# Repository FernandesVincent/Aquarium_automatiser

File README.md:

# Aquarium_automatiser
Suite du projet 2425_Maker_Aquarium

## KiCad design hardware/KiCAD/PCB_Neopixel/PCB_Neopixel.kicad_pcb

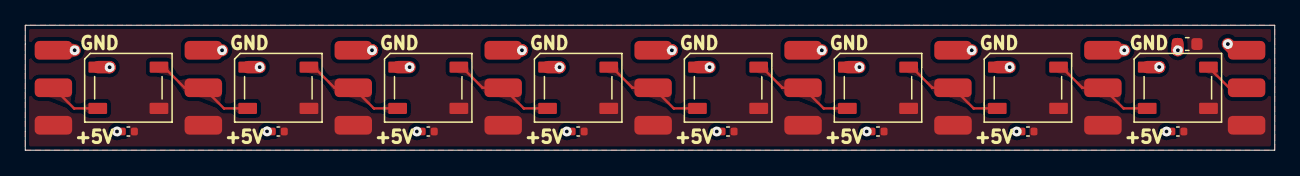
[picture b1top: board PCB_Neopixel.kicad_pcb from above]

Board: 2 copper layers, 100.0 x 10.0 mm, 44 parts (0 on the bottom side), 11 nets.

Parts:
C201, C301, C401, C501, C601, C701, C801, C901: 100n; C_0402_1005Metric
C1201: 10u; C_0603_1608Metric
D201, D301, D401, D501, D601, D701, D801, D901: WS2812B; LED_WS2812B_PLCC4_5.0x5.0mm_P3.2mm
J201, J202, J203, J301, J302, J303, J401, J402, J403, J501, J502, J503, J601, J602, J603, J701, J702, J703, J801, J802, J803, J901, J902, J903, J1201, J1202, J1203: Conn_01x01; SolderWirePad_1x01_SMD_1.5x3mm

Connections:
+5V: C201.1, C301.1, C401.1, C501.1, C601.1, C701.1, C801.1, C901.1, C1201.1, D201.1 (VDD), D301.1 (VDD), D401.1 (VDD), D501.1 (VDD), D601.1 (VDD), D701.1 (VDD), D801.1 (VDD), D901.1 (VDD), J201.1, J301.1, J401.1, J501.1, J601.1, J701.1, J801.1, J901.1, J1201.1
/Segment/DI: D201.4 (DIN), J203.1
DO1: D201.2 (DOUT), D301.4 (DIN), J303.1
DO2: D301.2 (DOUT), D401.4 (DIN), J403.1
DO3: D401.2 (DOUT), D501.4 (DIN), J503.1
DO4: D501.2 (DOUT), D601.4 (DIN), J603.1
DO5: D601.2 (DOUT), D701.4 (DIN), J703.1
DO6: D701.2 (DOUT), D801.4 (DIN), J803.1
DO7: D801.2 (DOUT), D901.4 (DIN), J903.1
DO8: D901.2 (DOUT), J1203.1
GND: C201.2, C301.2, C401.2, C501.2, C601.2, C701.2, C801.2, C901.2, C1201.2, D201.3 (VSS), D301.3 (VSS), D401.3 (VSS), D501.3 (VSS), D601.3 (VSS), D701.3 (VSS), D801.3 (VSS), D901.3 (VSS), J202.1, J302.1, J402.1, J502.1, J602.1, J702.1, J802.1, J902.1, J1202.1

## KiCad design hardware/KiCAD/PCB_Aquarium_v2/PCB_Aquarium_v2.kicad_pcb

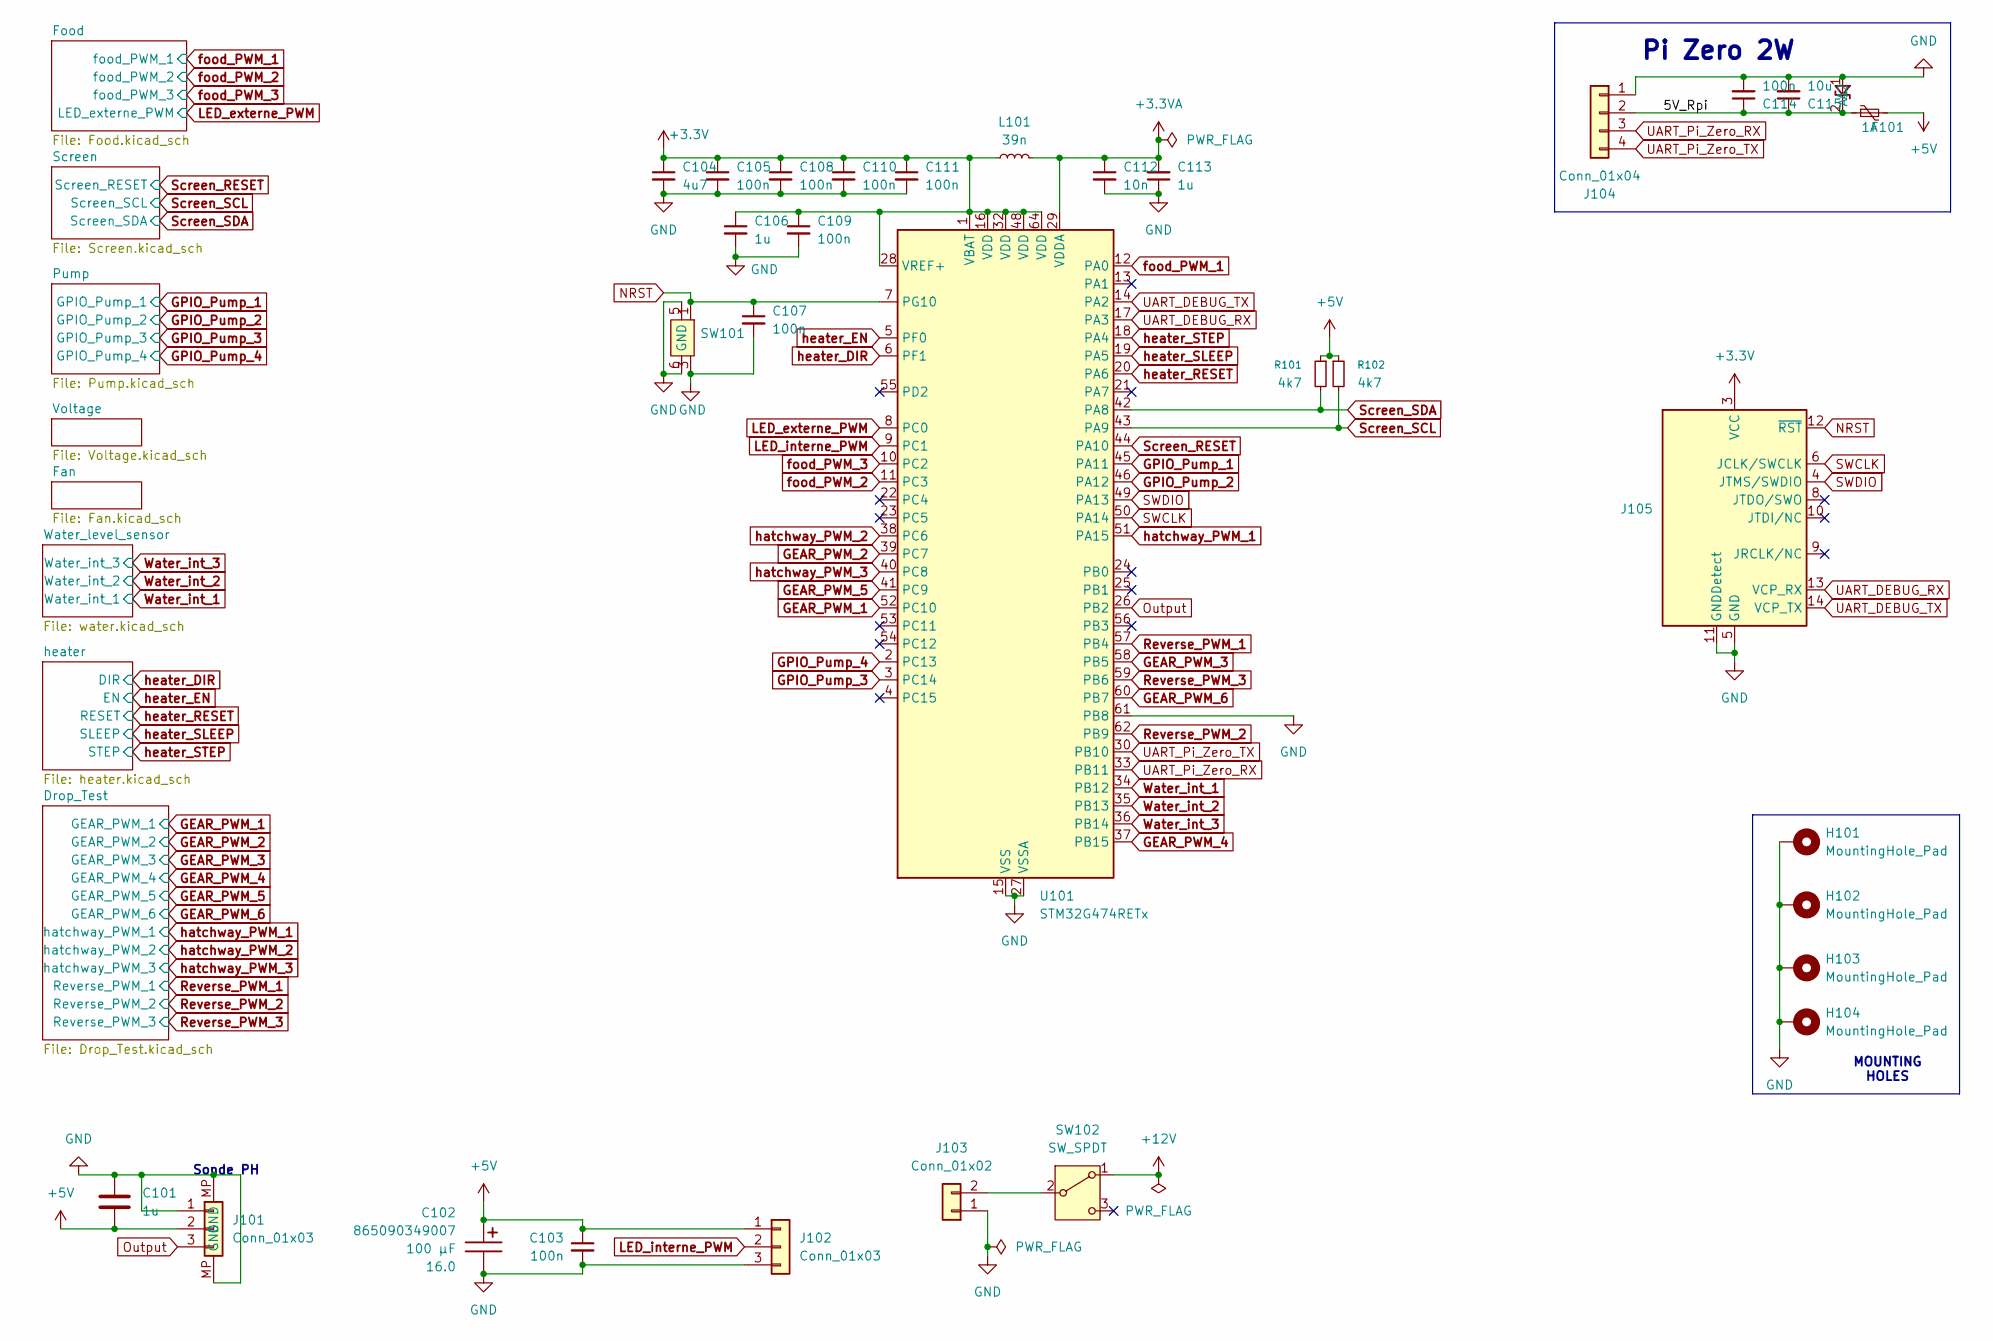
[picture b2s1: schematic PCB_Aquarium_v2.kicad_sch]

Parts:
C101: 1u; C_0603_1608Metric
C102: D8L6.5_865090349007; CP_Wurth_WCAP-ASLU-D8L6.5; Voltage 16.0; Part Number 865090349007
C103, C105, C107, C108, C109, C110, C111, C114: 100n; C_0402_1005Metric
C104: 4u7; C_0603_1608Metric
C106, C113: 1u; C_0402_1005Metric
C112: 10n; C_0402_1005Metric
C115: 10u; C_0603_1608Metric
D101: D_SOD-523
F101: 1A; Fuse_2920_7451Metric; MPN 0ZAF0013FF28
H101, H102, H103, H104: MountingHole_Pad; MountingHole_3.2mm_M3_Pad_Via
J101: Conn_01x03; JST_SH_BM03B-SRSS-TB_1x03-1MP_P1.00mm_Vertical
J102: Conn_01x03; JST_PH_B3B-PH-K_1x03_P2.00mm_Vertical
J103: Conn_01x02; AMASS_XT30U-M_1x02_P5.0mm_Vertical
J104: Conn_01x04; JST_PH_B4B-PH-K_1x04_P2.00mm_Vertical
J105: Conn_ST_STDC14; PinHeader_2x07_P1.27mm_Vertical_SMD; MPN STLINK-V3MINIE
L101: 39n; L_0603_1608Metric
R101, R102: 4k7; R_0201_0603Metric
SW101: WS-TASV SMT Tact Switch 3.0 x 2.6 mm
SW102: SW_SPDT; SW_Wurth_WS-TOTV_472123020421
U101: STM32G474RETx; LQFP-64_10x10mm_P0.5mm

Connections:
+3.3V: C104.1, C105.1, C106.1, C108.1, C109.1, C110.1, C111.1, J105.3 (VCC), L101.1, U101.1 (VBAT), U101.16 (VDD), U101.28 (VREF+), U101.32 (VDD), U101.48 (VDD), U101.64 (VDD); also elsewhere on the board
+3.3VA: C112.1, C113.2, L101.2, U101.29 (VDDA)
+5V: C101.1, C102.1, C103.1, F101.2, J101.2, J102.1, R101.1, R102.1; also elsewhere on the board
+12V: SW102.1 (A); also elsewhere on the board
/5V_Rpi: C114.1, C115.1, D101.2 (A2), F101.1, J104.2
GEAR_PWM_1: U101.52 (PC10); also elsewhere on the board
GEAR_PWM_2: U101.39 (PC7); also elsewhere on the board
GEAR_PWM_3: U101.58 (PB5); also elsewhere on the board
GEAR_PWM_4: U101.37 (PB15); also elsewhere on the board
GEAR_PWM_5: U101.41 (PC9); also elsewhere on the board
GEAR_PWM_6: U101.60 (PB7); also elsewhere on the board
GND: C101.2, C102.2, C103.2, C104.2, C105.2, C106.2, C107.2, C108.2, C109.2, C110.2, C111.2, C112.2, C113.1, C114.2, C115.2, D101.1 (A1), H101.1, H102.1, H103.1, H104.1, J101.1, J101.MP (GND), J102.3, J103.1, J104.1, J105.5 (GND), J105.7 (GND), J105.11 (GNDDetect), SW101.3, SW101.4, SW101.5, SW101.6 (GND), U101.15 (VSS), U101.27 (VSSA), U101.31 (VSS), U101.47 (VSS), U101.61 (PB8), U101.63 (VSS); also elsewhere on the board
GPIO_Pump_1: U101.45 (PA11); also elsewhere on the board
GPIO_Pump_2: U101.46 (PA12); also elsewhere on the board
GPIO_Pump_3: U101.3 (PC14); also elsewhere on the board
GPIO_Pump_4: U101.2 (PC13); also elsewhere on the board
LED_externe_PWM: U101.8 (PC0); also elsewhere on the board
LED_interne_PWM: J102.2, U101.9 (PC1)
NRST: C107.1, J105.12 (~RST), SW101.1, SW101.2, U101.7 (PG10)
unnamed: J103.2, SW102.2 (B)
Output: J101.3, U101.26 (PB2)
Reverse_PWM_1: U101.57 (PB4); also elsewhere on the board
Reverse_PWM_2: U101.62 (PB9); also elsewhere on the board
Reverse_PWM_3: U101.59 (PB6); also elsewhere on the board
SWCLK: J105.6 (JCLK/SWCLK), U101.50 (PA14)
SWDIO: J105.4 (JTMS/SWDIO), U101.49 (PA13)
Screen_RESET: U101.44 (PA10); also elsewhere on the board
Screen_SCL: R102.2, U101.43 (PA9); also elsewhere on the board
Screen_SDA: R101.2, U101.42 (PA8); also elsewhere on the board
UART_DEBUG_RX: J105.13 (VCP_RX), U101.17 (PA3)
UART_DEBUG_TX: J105.14 (VCP_TX), U101.14 (PA2)
UART_Pi_Zero_RX: J104.3, U101.33 (PB11)
UART_Pi_Zero_TX: J104.4, U101.30 (PB10)
Water_int_1: U101.34 (PB12); also elsewhere on the board
Water_int_2: U101.35 (PB13); also elsewhere on the board
Water_int_3: U101.36 (PB14); also elsewhere on the board
food_PWM_1: U101.12 (PA0); also elsewhere on the board
food_PWM_2: U101.11 (PC3); also elsewhere on the board
food_PWM_3: U101.10 (PC2); also elsewhere on the board
hatchway_PWM_1: U101.51 (PA15); also elsewhere on the board
hatchway_PWM_2: U101.38 (PC6); also elsewhere on the board
hatchway_PWM_3: U101.40 (PC8); also elsewhere on the board
heater_DIR: U101.6 (PF1); also elsewhere on the board
heater_EN: U101.5 (PF0); also elsewhere on the board
heater_RESET: U101.20 (PA6); also elsewhere on the board
heater_SLEEP: U101.19 (PA5); also elsewhere on the board
heater_STEP: U101.18 (PA4); also elsewhere on the board

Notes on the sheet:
Sonde PH
Pi Zero 2W
MOUNTING HOLES

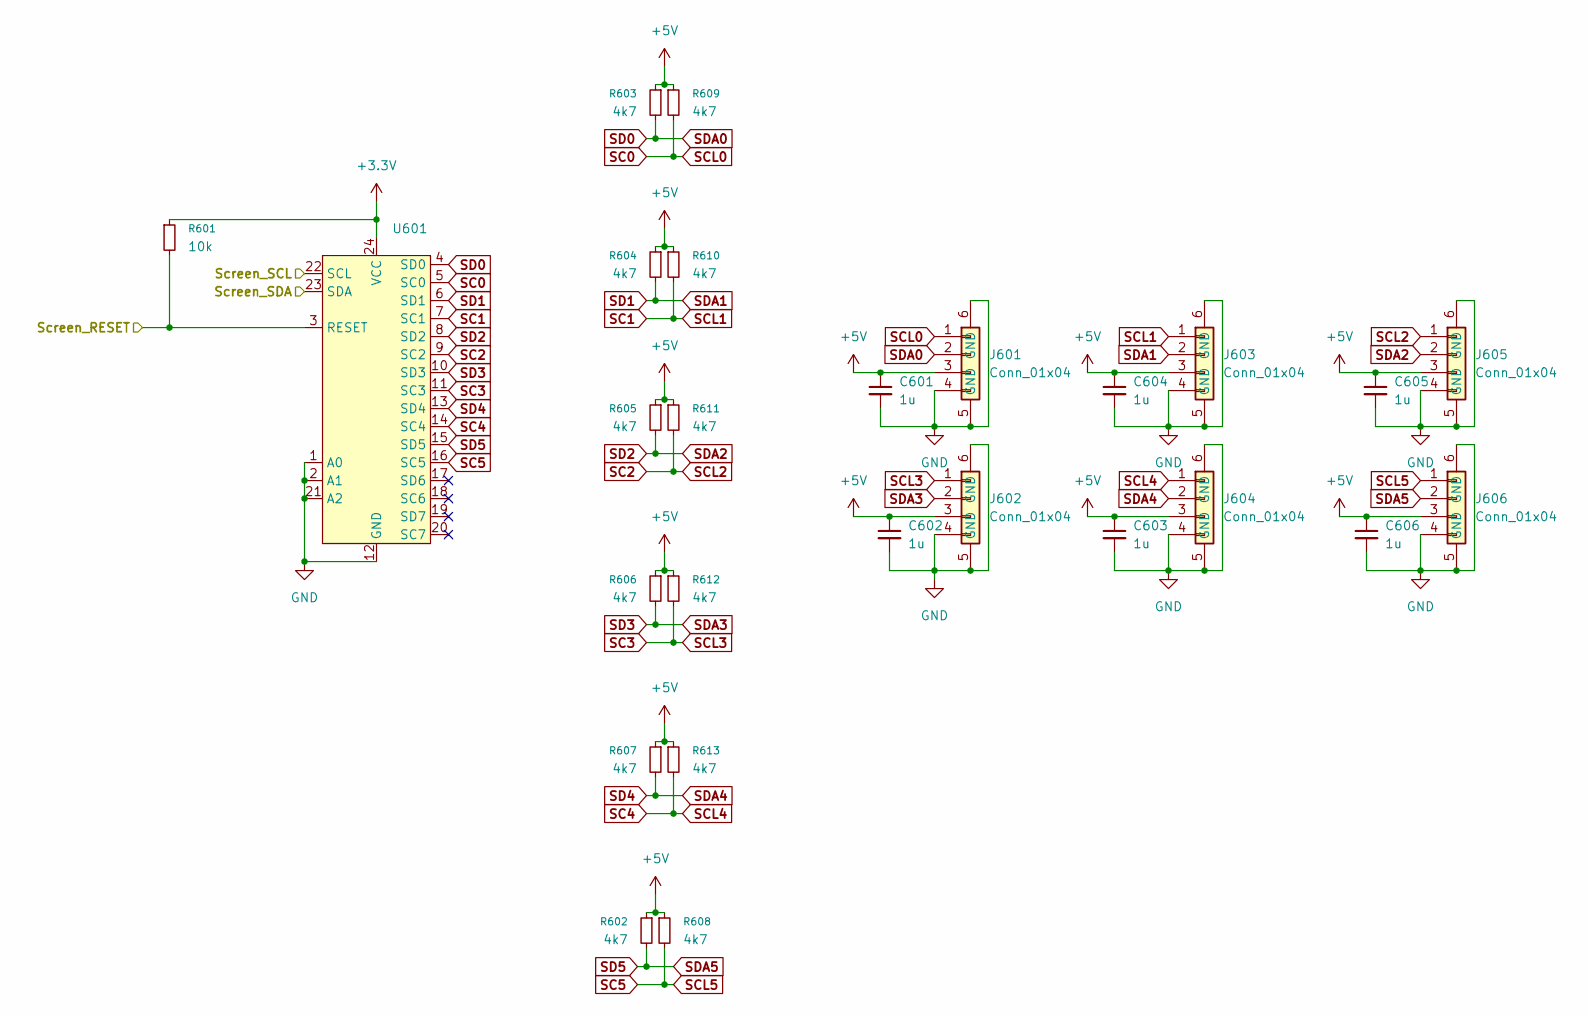
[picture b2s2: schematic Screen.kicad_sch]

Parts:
C601, C602, C603, C604, C605, C606: 1u; C_0603_1608Metric
J601, J602, J603, J604, J605, J606: Conn_01x04; Wurth_Vertical_4_pos_0.8mm
R601: 10k; R_0402_1005Metric
R602, R603, R604, R605, R606, R607, R608, R609, R610, R611, R612, R613: 4k7; R_0201_0603Metric
U601: TSSOP-24_4.4x7.8mm_P0.65mm; MPN PI4MSD5V9547LEX

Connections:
+3.3V: R601.1, U601.24 (VCC); also elsewhere on the board
+5V: C601.1, C602.1, C603.1, C604.1, C605.1, C606.1, J601.3, J602.3, J603.3, J604.3, J605.3, J606.3, R602.1, R603.1, R604.1, R605.1, R606.1, R607.1, R608.1, R609.1, R610.1, R611.1, R612.1, R613.1; also elsewhere on the board
GND: C601.2, C602.2, C603.2, C604.2, C605.2, C606.2, J601.4, J601.5 (GND), J601.6 (GND), J602.4, J602.5 (GND), J602.6 (GND), J603.4, J603.5 (GND), J603.6 (GND), J604.4, J604.5 (GND), J604.6 (GND), J605.4, J605.5 (GND), J605.6 (GND), J606.4, J606.5 (GND), J606.6 (GND), U601.1 (A0), U601.2 (A1), U601.12 (GND), U601.21 (A2); also elsewhere on the board
SC0: J601.1, R609.2, U601.5 (SC0)
SC1: J603.1, R610.2, U601.7 (SC1)
SC2: J605.1, R611.2, U601.9 (SC2)
SC3: J602.1, R612.2, U601.11 (SC3)
SC4: J604.1, R613.2, U601.14 (SC4)
SC5: J606.1, R608.2, U601.16 (SC5)
SD0: J601.2, R603.2, U601.4 (SD0)
SD1: J603.2, R604.2, U601.6 (SD1)
SD2: J605.2, R605.2, U601.8 (SD2)
SD3: J602.2, R606.2, U601.10 (SD3)
SD4: J604.2, R607.2, U601.13 (SD4)
SD5: J606.2, R602.2, U601.15 (SD5)
Screen_RESET: R601.2, U601.3 (RESET); also elsewhere on the board
Screen_SCL: U601.22 (SCL); also elsewhere on the board
Screen_SDA: U601.23 (SDA); also elsewhere on the board

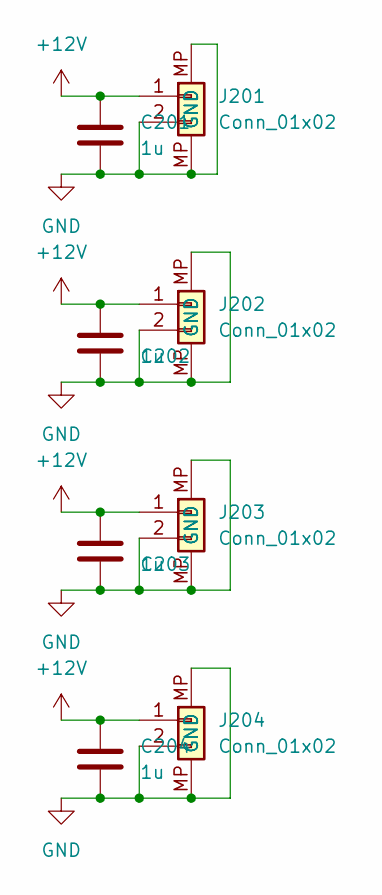
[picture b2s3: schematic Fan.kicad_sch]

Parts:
C201, C202, C203, C204: 1u; C_0603_1608Metric
J201, J202, J203, J204: Conn_01x02; JST_SH_BM02B-SRSS-TB_1x02-1MP_P1.00mm_Vertical

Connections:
+12V: C201.2, C202.2, C203.2, C204.2, J201.1, J202.1, J203.1, J204.1; also elsewhere on the board
GND: C201.1, C202.1, C203.1, C204.1, J201.2, J201.MP (GND), J202.2, J202.MP (GND), J203.2, J203.MP (GND), J204.2, J204.MP (GND); also elsewhere on the board

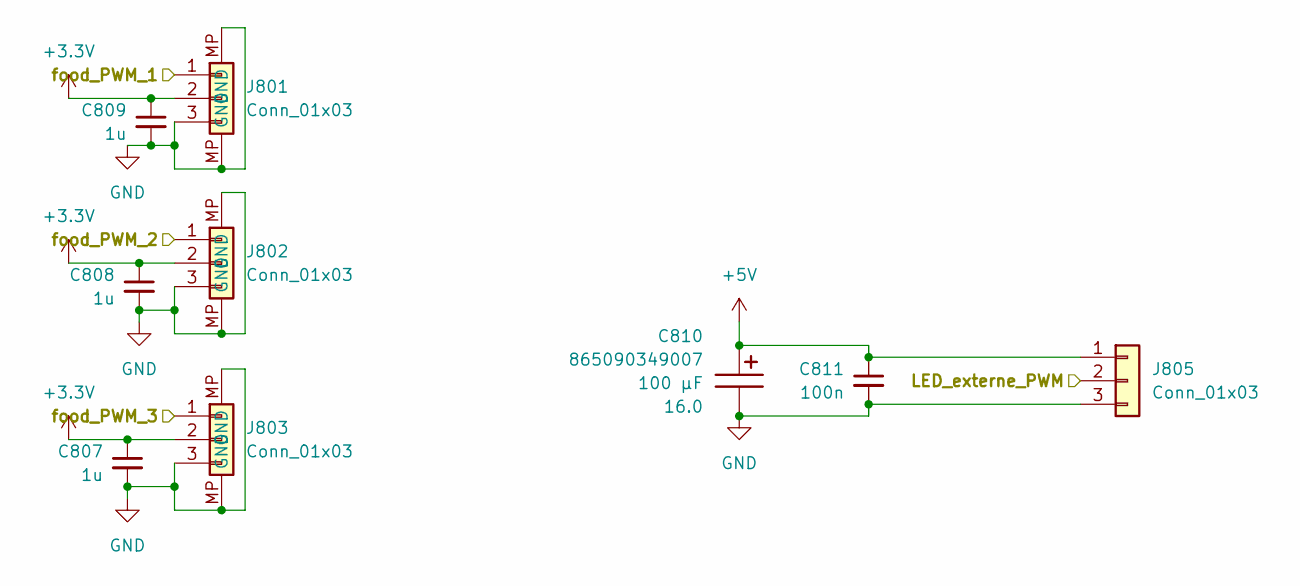
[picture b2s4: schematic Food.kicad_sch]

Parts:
C807, C808, C809: 1u; C_0603_1608Metric
C810: D8L6.5_865090349007; CP_Wurth_WCAP-ASLU-D8L6.5; Voltage 16.0; Part Number 865090349007
C811: 100n; C_0402_1005Metric
J801, J802, J803: Conn_01x03; JST_SH_BM03B-SRSS-TB_1x03-1MP_P1.00mm_Vertical
J805: Conn_01x03; JST_PH_B3B-PH-K_1x03_P2.00mm_Vertical

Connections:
+3.3V: C807.1, C808.1, C809.1, J801.2, J802.2, J803.2; also elsewhere on the board
+5V: C810.1, C811.1, J805.1; also elsewhere on the board
GND: C807.2, C808.2, C809.2, C810.2, C811.2, J801.3, J801.MP (GND), J802.3, J802.MP (GND), J803.3, J803.MP (GND), J805.3; also elsewhere on the board
LED_externe_PWM: J805.2; also elsewhere on the board
food_PWM_1: J801.1; also elsewhere on the board
food_PWM_2: J802.1; also elsewhere on the board
food_PWM_3: J803.1; also elsewhere on the board

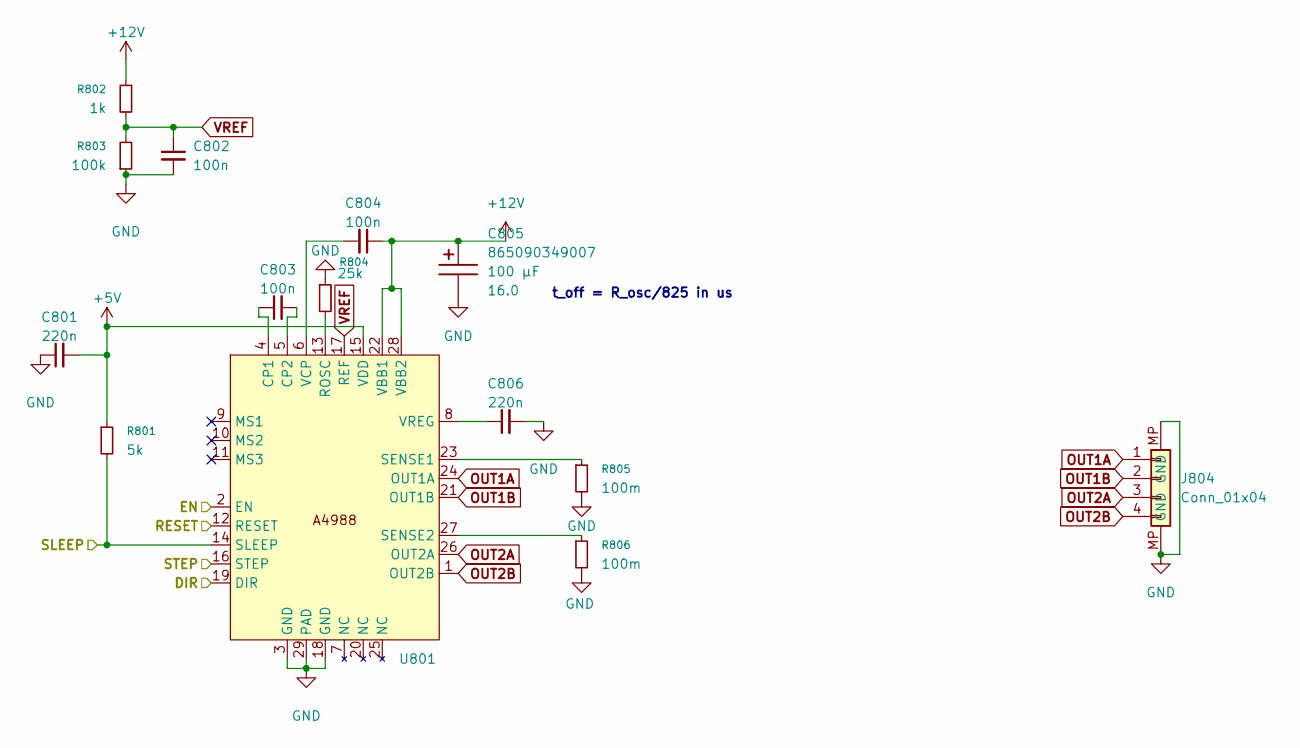
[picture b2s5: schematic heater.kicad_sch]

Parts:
C801, C806: 220n; C_0402_1005Metric
C802, C803, C804: 100n; C_0402_1005Metric
C805: D8L6.5_865090349007; CP_Wurth_WCAP-ASLU-D8L6.5; Voltage 16.0; Part Number 865090349007
J804: Conn_01x04; JST_SH_BM04B-SRSS-TB_1x04-1MP_P1.00mm_Vertical
R801: 5k; R_0402_1005Metric
R802: 1k; R_0402_1005Metric
R803: 100k; R_0402_1005Metric
R804: 25k; R_0402_1005Metric
R805, R806: 100m; R_0603_1608Metric; MPN 560050316001
U801: QFN-28-1EP_5x5mm_P0.5mm_EP2.7x2.7mm

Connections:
+5V: C801.2, R801.1, U801.15 (VDD); also elsewhere on the board
+12V: C804.1, C805.1, R802.1, U801.22 (VBB1), U801.28 (VBB2); also elsewhere on the board
GND: C801.1, C802.2, C805.2, C806.2, J804.MP (GND), R803.1, R804.1, R805.2, R806.2, U801.3 (GND), U801.18 (GND), U801.29 (PAD); also elsewhere on the board
unnamed: C803.1, U801.4 (CP1)
unnamed: C803.2, U801.5 (CP2)
unnamed: R804.2, U801.13 (ROSC)
unnamed: R805.1, U801.23 (SENSE1)
unnamed: R806.1, U801.27 (SENSE2)
unnamed: C804.2, U801.6 (VCP)
unnamed: C806.1, U801.8 (VREG)
OUT1A: J804.1, U801.24 (OUT1A)
OUT1B: J804.2, U801.21 (OUT1B)
OUT2A: J804.3, U801.26 (OUT2A)
OUT2B: J804.4, U801.1 (OUT2B)
VREF: C802.1, R802.2, R803.2, U801.17 (REF)
heater_DIR: U801.19 (DIR); also elsewhere on the board
heater_EN: U801.2 (EN); also elsewhere on the board
heater_RESET: U801.12 (RESET); also elsewhere on the board
heater_SLEEP: R801.2, U801.14 (SLEEP); also elsewhere on the board
heater_STEP: U801.16 (STEP); also elsewhere on the board

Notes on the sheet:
t_off = R_osc/825 in us

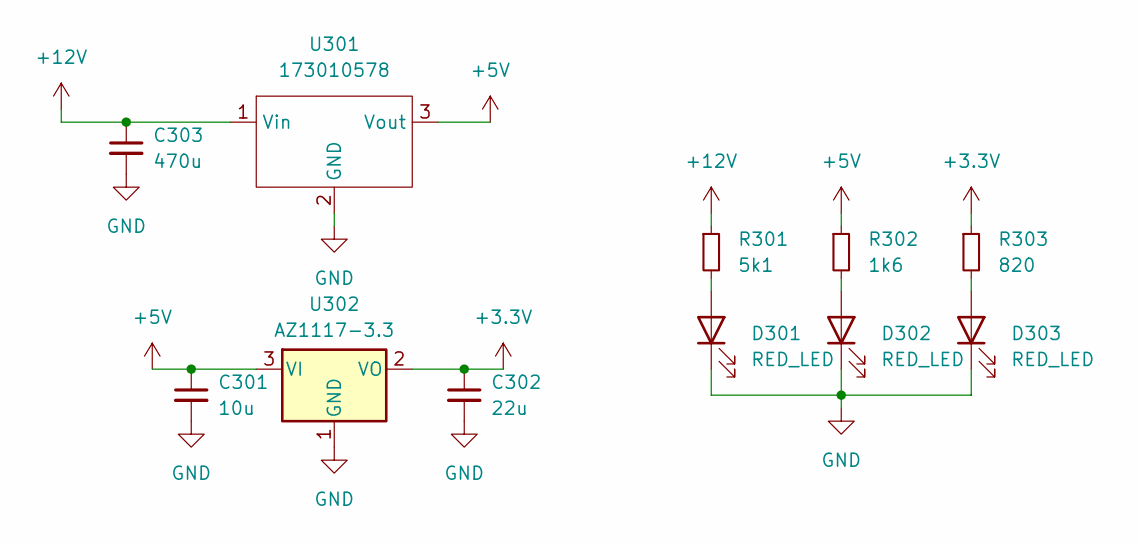
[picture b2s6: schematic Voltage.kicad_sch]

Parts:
C301: 10u; C_0603_1608Metric
C302: 22u; C_Elec_5x5.4
C303: 470u; C_Elec_10x10.2
D301, D302, D303: RED_LED; LED_0603_1608Metric; MPN 150060RS55040
R301: 5k1; R_0402_1005Metric
R302: 1k6; R_0402_1005Metric
R303: 820; R_0402_1005Metric
U301: 173010578; 173010542; MPN 173010578
U302: AZ1117-3.3; SOT-223-3_TabPin2; MPN AZ1117CH2-3.3TRG1

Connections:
+3.3V: C302.1, R303.1, U302.2 (VO); also elsewhere on the board
+5V: C301.1, R302.1, U301.3 (Vout), U302.3 (VI); also elsewhere on the board
+12V: C303.1, R301.1, U301.1 (Vin); also elsewhere on the board
GND: C301.2, C302.2, C303.2, D301.1 (K), D302.1 (K), D303.1 (K), U301.2 (GND), U302.1 (GND); also elsewhere on the board
unnamed: D301.2 (A), R301.2
unnamed: D302.2 (A), R302.2
unnamed: D303.2 (A), R303.2

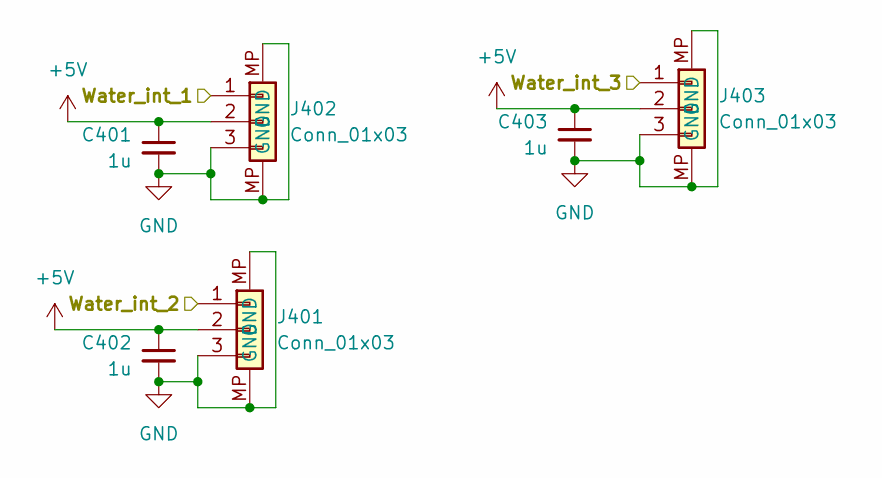
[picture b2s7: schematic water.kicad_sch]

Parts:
C401, C402, C403: 1u; C_0603_1608Metric
J401, J402, J403: Conn_01x03; JST_SH_BM03B-SRSS-TB_1x03-1MP_P1.00mm_Vertical

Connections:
+5V: C401.1, C402.1, C403.1, J401.2, J402.2, J403.2; also elsewhere on the board
GND: C401.2, C402.2, C403.2, J401.3, J401.MP (GND), J402.3, J402.MP (GND), J403.3, J403.MP (GND); also elsewhere on the board
Water_int_1: J402.1; also elsewhere on the board
Water_int_2: J401.1; also elsewhere on the board
Water_int_3: J403.1; also elsewhere on the board

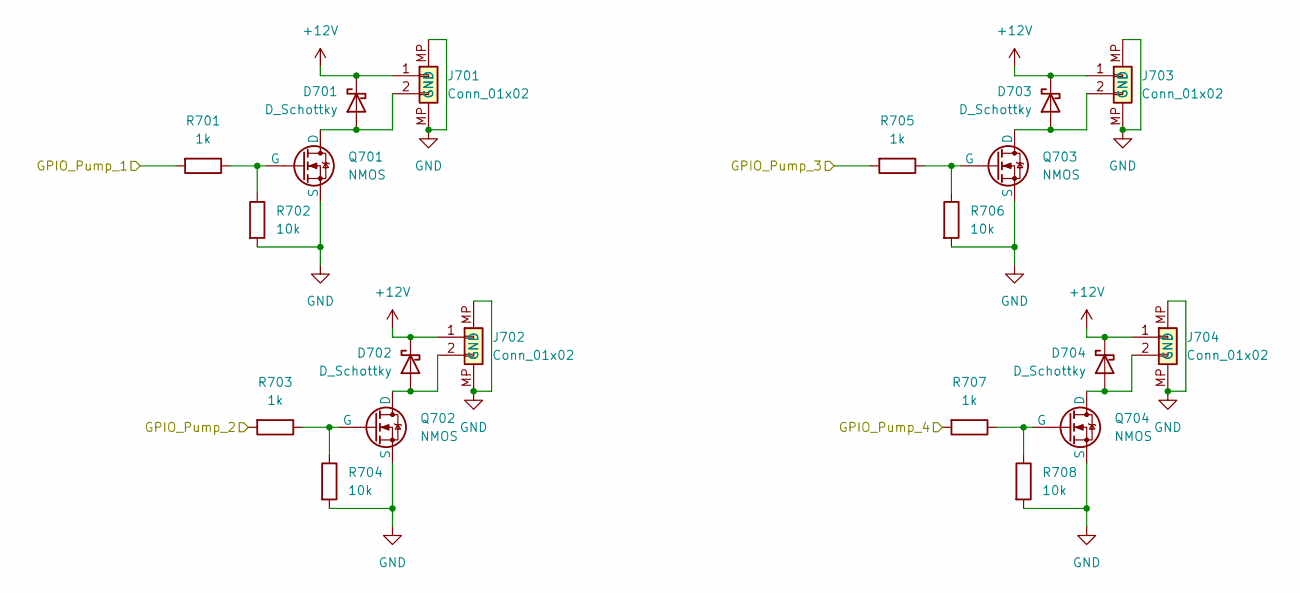
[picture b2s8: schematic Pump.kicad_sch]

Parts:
D701, D702, D703, D704: D_Schottky; FSV330AF; MPN FSV340AF
J701, J702, J703, J704: Conn_01x02; JST_SH_BM02B-SRSS-TB_1x02-1MP_P1.00mm_Vertical
Q701, Q702, Q703, Q704: NMOS; SOT-23; MPN SQ2310ES-T1_BE3
R701, R703, R705, R707: 1k; R_0402_1005Metric
R702, R704, R706, R708: 10k; R_0402_1005Metric

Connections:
+12V: D701.1 (K), D702.1 (K), D703.1 (K), D704.1 (K), J701.1, J702.1, J703.1, J704.1; also elsewhere on the board
GND: J701.MP (GND), J702.MP (GND), J703.MP (GND), J704.MP (GND), Q701.3 (S), Q702.3 (S), Q703.3 (S), Q704.3 (S), R702.2, R704.2, R706.2, R708.2; also elsewhere on the board
GPIO_Pump_1: R701.2; also elsewhere on the board
GPIO_Pump_2: R703.2; also elsewhere on the board
GPIO_Pump_3: R705.2; also elsewhere on the board
GPIO_Pump_4: R707.2; also elsewhere on the board
unnamed: D701.2 (A), J701.2, Q701.1 (D)
unnamed: D702.2 (A), J702.2, Q702.1 (D)
unnamed: D703.2 (A), J703.2, Q703.1 (D)
unnamed: D704.2 (A), J704.2, Q704.1 (D)
unnamed: Q701.2 (G), R701.1, R702.1
unnamed: Q702.2 (G), R703.1, R704.1
unnamed: Q703.2 (G), R705.1, R706.1
unnamed: Q704.2 (G), R707.1, R708.1

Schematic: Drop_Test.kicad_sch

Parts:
C901, C902, C903, C904, C905, C906, C907, C908, C909, C910, C911, C912: 1u; C_0603_1608Metric
J901, J902, J903, J904, J905, J906, J907, J908, J909, J910, J911, J912: Conn_01x03; JST_SH_BM03B-SRSS-TB_1x03-1MP_P1.00mm_Vertical

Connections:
+3.3V: C901.1, C902.1, C903.1, C904.1, C905.1, C906.1, C907.1, C908.1, C909.1, C910.1, C911.1, C912.1, J901.2, J902.2, J903.2, J904.2, J905.2, J906.2, J907.2, J908.2, J909.2, J910.2, J911.2, J912.2; also elsewhere on the board
GEAR_PWM_1: J909.1; also elsewhere on the board
GEAR_PWM_2: J907.1; also elsewhere on the board
GEAR_PWM_3: J908.1; also elsewhere on the board
GEAR_PWM_4: J906.1; also elsewhere on the board
GEAR_PWM_5: J904.1; also elsewhere on the board
GEAR_PWM_6: J905.1; also elsewhere on the board
GND: C901.2, C902.2, C903.2, C904.2, C905.2, C906.2, C907.2, C908.2, C909.2, C910.2, C911.2, C912.2, J901.3, J901.MP (GND), J902.3, J902.MP (GND), J903.3, J903.MP (GND), J904.3, J904.MP (GND), J905.3, J905.MP (GND), J906.3, J906.MP (GND), J907.3, J907.MP (GND), J908.3, J908.MP (GND), J909.3, J909.MP (GND), J910.3, J910.MP (GND), J911.3, J911.MP (GND), J912.3, J912.MP (GND); also elsewhere on the board
Reverse_PWM_1: J903.1; also elsewhere on the board
Reverse_PWM_2: J901.1; also elsewhere on the board
Reverse_PWM_3: J902.1; also elsewhere on the board
hatchway_PWM_1: J912.1; also elsewhere on the board
hatchway_PWM_2: J910.1; also elsewhere on the board
hatchway_PWM_3: J911.1; also elsewhere on the board

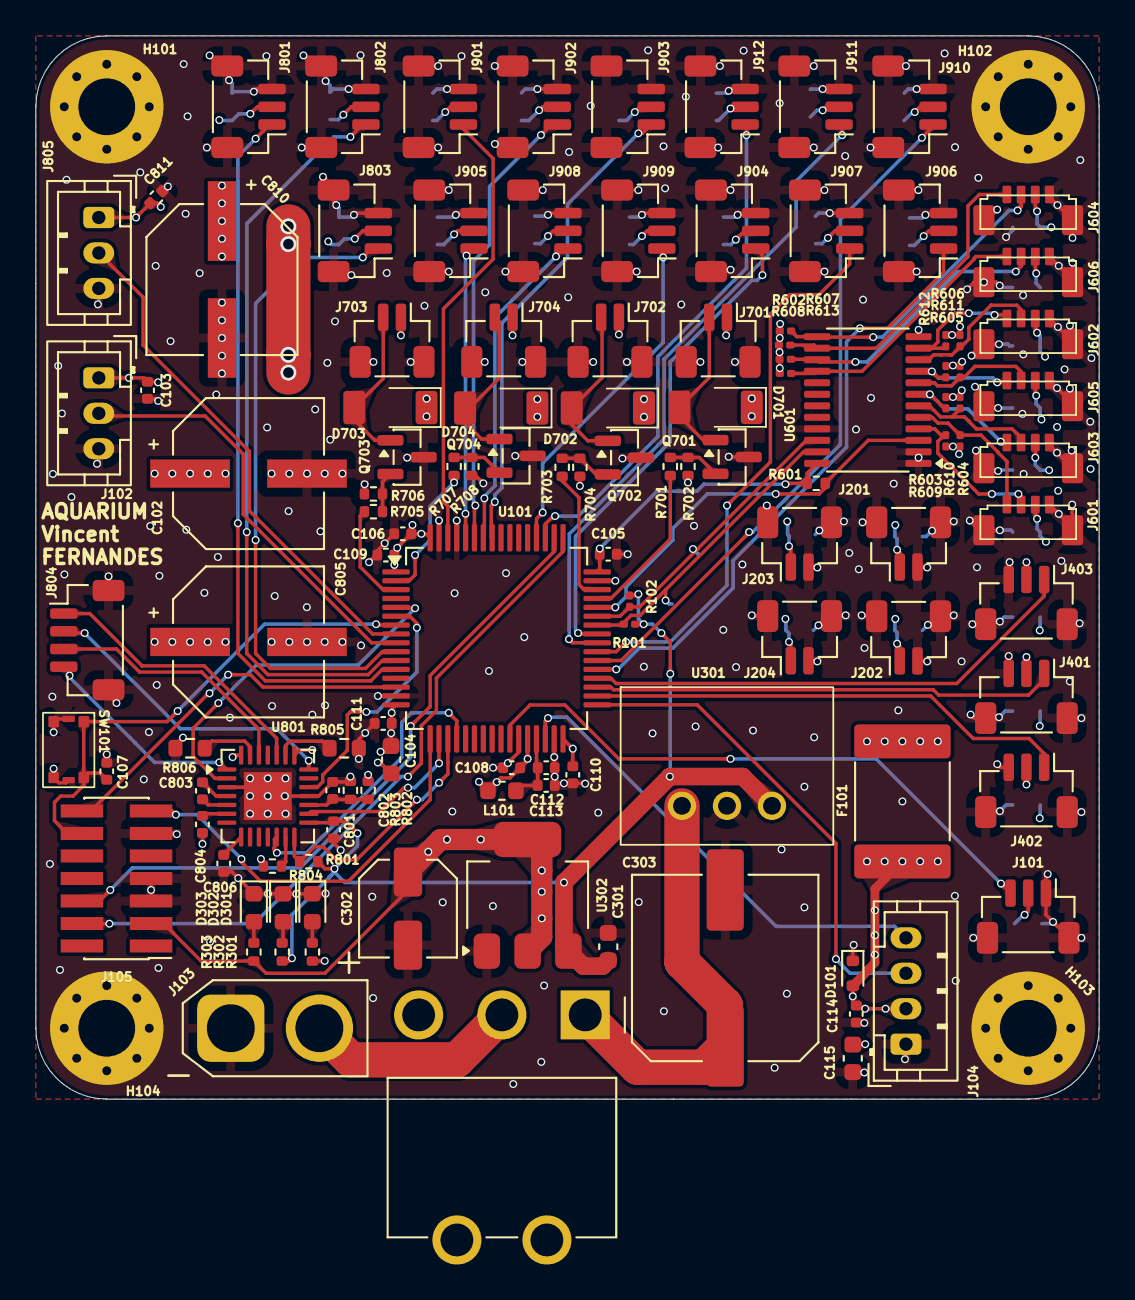
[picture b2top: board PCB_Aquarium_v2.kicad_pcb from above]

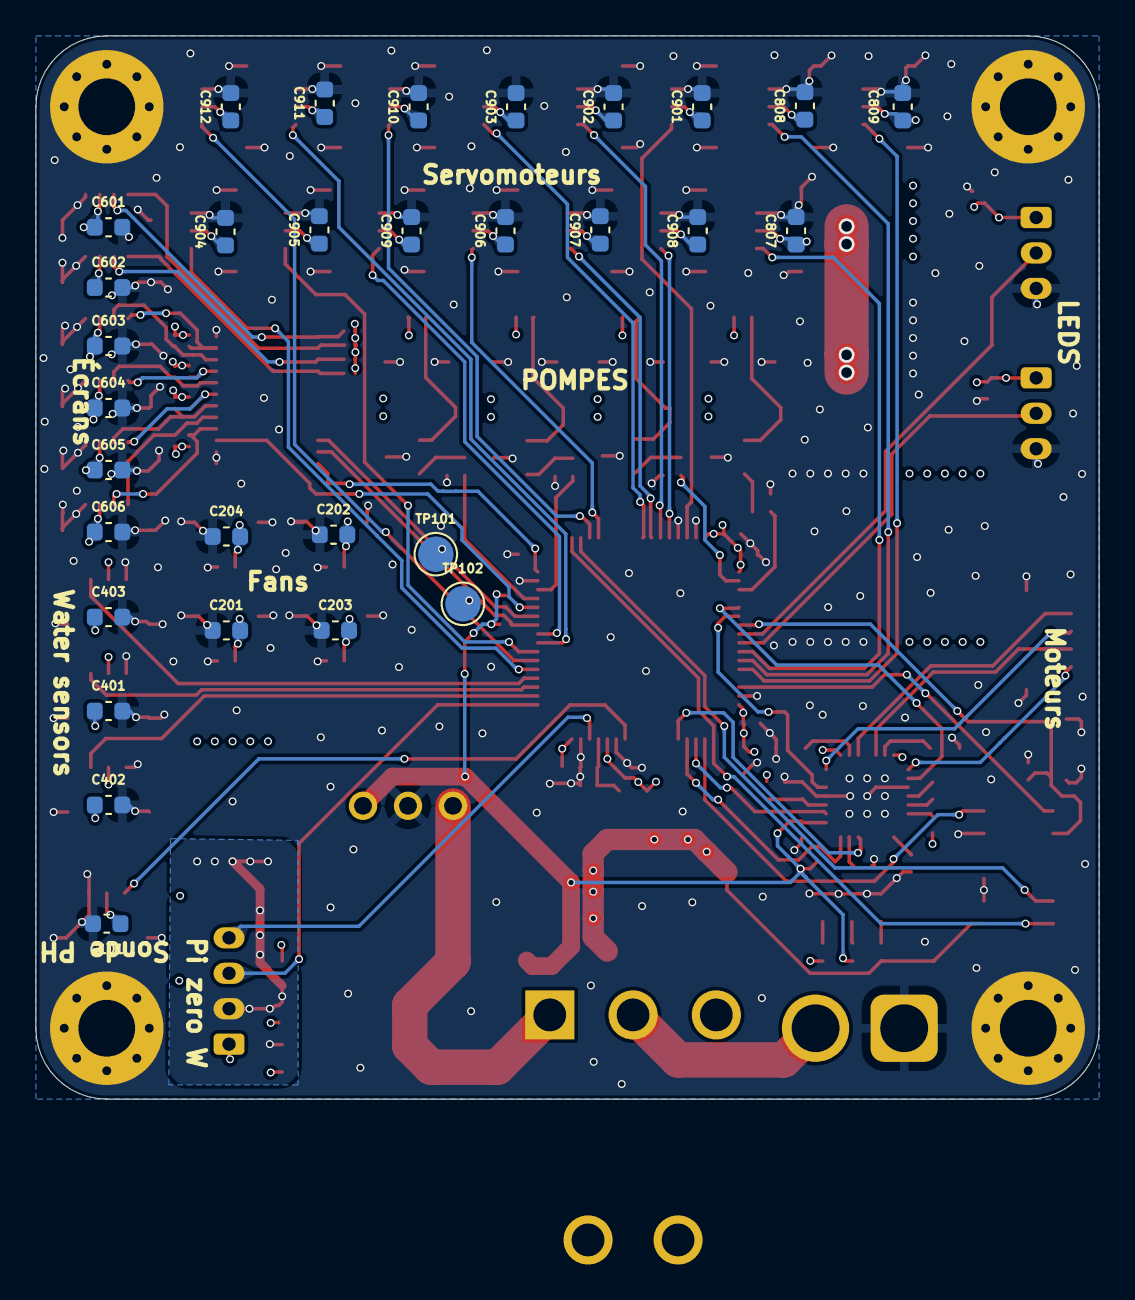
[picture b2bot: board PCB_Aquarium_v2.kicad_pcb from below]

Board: 4 copper layers, 60.0 x 60.0 mm, 152 parts (31 on the bottom side), 82 nets.

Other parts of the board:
TP101, TP102: TestPoint; TestPoint_Pad_D2.0mm

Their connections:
Screen_SCL: TP101.1; also elsewhere on the board
Screen_SDA: TP102.1; also elsewhere on the board

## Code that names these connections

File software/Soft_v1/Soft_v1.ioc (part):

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Mcu.Name=STM32G474R(B-C-E)Tx
Mcu.Package=LQFP64
Mcu.UserName=STM32G474RETx
PA0.GPIOParameters=GPIO_Label
PA0.GPIO_Label=food_PWM_1
PA0.Signal=S_TIM2_CH1
PA10.GPIOParameters=GPIO_Label
PA10.GPIO_Label=Screen_RESET
PA10.Signal=GPIO_Output
PA11.GPIOParameters=GPIO_Label
PA11.GPIO_Label=GPIO_Pump_1
PA11.Signal=GPIO_Output
PA12.GPIOParameters=GPIO_Label
PA12.GPIO_Label=GPIO_Pump_2
PA12.Signal=GPIO_Output
PA13.Mode=Serial_Wire
PA13.Signal=SYS_JTMS-SWDIO
PA14.Mode=Serial_Wire
PA14.Signal=SYS_JTCK-SWCLK
PA15.GPIOParameters=GPIO_Label
PA15.GPIO_Label=hatchway_PWM_1
PA15.Signal=S_TIM8_CH1
PA2.GPIOParameters=GPIO_Label
PA2.GPIO_Label=UART_DEBUG_TX
PA2.Mode=Asynchronous
PA2.Signal=USART2_TX
PA3.GPIOParameters=GPIO_Label
PA3.GPIO_Label=UART_DEBUG_RX
PA3.Mode=Asynchronous
PA3.Signal=USART2_RX
PA4.GPIOParameters=GPIO_Label
PA4.GPIO_Label=heater_STEP
PA4.Signal=GPIO_Output
PA5.GPIOParameters=GPIO_Label
PA5.GPIO_Label=heater_SLEEP
PA5.Signal=GPIO_Output
PA6.GPIOParameters=GPIO_Label
PA6.GPIO_Label=heater_RESET
PA6.Signal=GPIO_Output
PA8.GPIOParameters=GPIO_Label
PA8.GPIO_Label=Screen_SDA
PA8.Mode=I2C
PA8.Signal=I2C2_SDA
PA9.GPIOParameters=GPIO_Label
PA9.GPIO_Label=Screen_SCL
PA9.Mode=I2C
PA9.Signal=I2C2_SCL
PB10.GPIOParameters=GPIO_Label
PB10.GPIO_Label=UART_Raspi_TX
PB10.Mode=Asynchronous
PB10.Signal=USART3_TX
PB11.GPIOParameters=GPIO_Label
PB11.GPIO_Label=UART_Raspi_RX
PB11.Mode=Asynchronous
PB11.Signal=USART3_RX
PB12.GPIOParameters=GPIO_Label
PB12.GPIO_Label=Water_int_1
PB12.Signal=GPXTI12
PB13.GPIOParameters=GPIO_Label
PB13.GPIO_Label=Water_int_2
PB13.Signal=GPXTI13
PB14.GPIOParameters=GPIO_Label
PB14.GPIO_Label=Water_int_3
PB14.Signal=GPXTI14
PB15.GPIOParameters=GPIO_Label
PB15.GPIO_Label=gear_PWM_4
PB15.Signal=S_TIM15_CH2
PB2.GPIOParameters=GPIO_Label
PB2.GPIO_Label=ADC_pH_input
PB2.Signal=ADC2_IN12
PB4.GPIOParameters=GPIO_Label
PB4.GPIO_Label=Reverse_PWM_1
PB4.Signal=S_TIM16_CH1
PB5.GPIOParameters=GPIO_Label
PB5.GPIO_Label=gear_PWM_3
PB5.Signal=S_TIM17_CH1
PB6.GPIOParameters=GPIO_Label
PB6.GPIO_Label=Reverse_PWM_3N
PB6.Signal=TIM16_CH1N
PB7.GPIOParameters=GPIO_Label
PB7.GPIO_Label=gear_PWM_6
PB7.Signal=S_TIM4_CH2
PB9.GPIOParameters=GPIO_Label
PB9.GPIO_Label=Reverse_PWM_2
PB9.Signal=S_TIM4_CH4
PC0.GPIOParameters=GPIO_Label
PC0.GPIO_Label=LED_externe_PWM
PC0.Signal=S_TIM1_CH1
PC1.GPIOParameters=GPIO_Label
PC1.GPIO_Label=LED_interne_PWM
PC1.Signal=S_TIM1_CH2
PC10.GPIOParameters=GPIO_Label
PC10.GPIO_Label=gear_PWM_1N
PC10.Signal=TIM8_CH1N
PC13.GPIOParameters=GPIO_Label
PC13.GPIO_Label=GPIO_Pump_4
PC13.Signal=GPIO_Output
PC14-OSC32_IN.GPIOParameters=GPIO_Label
PC14-OSC32_IN.GPIO_Label=GPIO_Pump_3
PC14-OSC32_IN.Signal=GPIO_Output
PC2.GPIOParameters=GPIO_Label
PC2.GPIO_Label=food_PWM_3
PC2.Signal=S_TIM1_CH3
PC3.GPIOParameters=GPIO_Label
PC3.GPIO_Label=food_PWM_2
PC3.Signal=S_TIM1_CH4
PC6.GPIOParameters=GPIO_Label
PC6.GPIO_Label=hatchway_PWM_2
PC6.Signal=S_TIM3_CH1
PC7.GPIOParameters=GPIO_Label
PC7.GPIO_Label=gear_PWM_2
PC7.Signal=S_TIM3_CH2
PC8.GPIOParameters=GPIO_Label
PC8.GPIO_Label=hatchway_PWM_3
PC8.Signal=S_TIM3_CH3
PC9.GPIOParameters=GPIO_Label
PC9.GPIO_Label=gear_PWM_5
PC9.Signal=S_TIM3_CH4
PF0-OSC_IN.GPIOParameters=GPIO_Label
PF0-OSC_IN.GPIO_Label=heater_EN
PF0-OSC_IN.Signal=GPIO_Output
PF1-OSC_OUT.GPIOParameters=GPIO_Label
PF1-OSC_OUT.GPIO_Label=heater_DIR
PF1-OSC_OUT.Signal=GPIO_Output
PG10-NRST.Signal=GPXTI10
RCC.HSE_VALUE=8000000
RCC.SYSCLKFreq_VALUE=16000000
board=custom

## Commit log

2026-01-30 classic folders
2026-01-30 txt files in folders
2026-01-30 Ajouté(e) Aquarium_v2.drawio
2026-01-30 Mettre à jour Aquarium_v2.drawio
2026-01-30 some starting files
2026-02-02 update sch pcb
2026-02-05 PCB principal finis
2026-02-11 PCB Neopixel
2026-02-12 PCB 100x10
2026-02-12 commited pi python code for color detection + uart w/nucleo + nucleo code for lcd screens
2026-02-12 PCB neopixel rigid done
